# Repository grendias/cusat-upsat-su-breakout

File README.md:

# QB50 SU Connector breakout

A breakout board for the QB50 mNLP Science Unit connector.

## License

Licensed under the [CERN OHLv1.2](LICENSE).

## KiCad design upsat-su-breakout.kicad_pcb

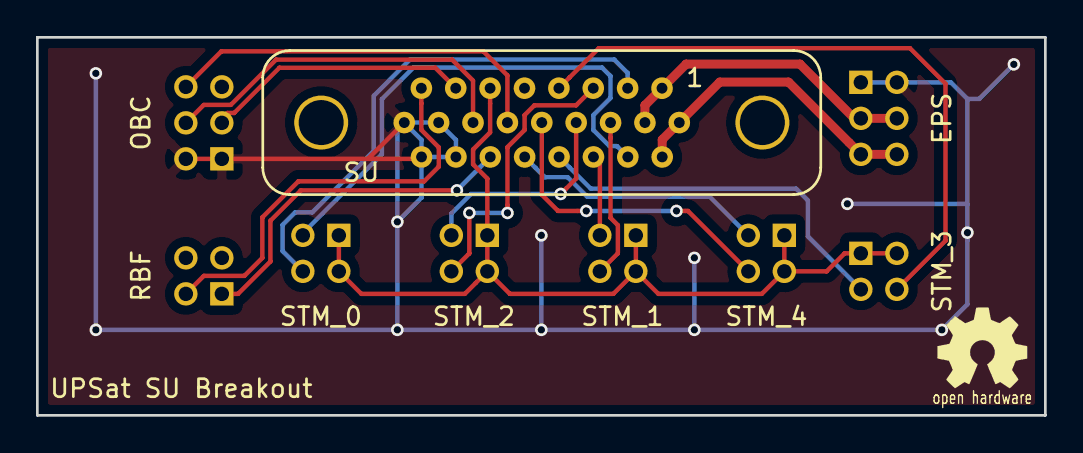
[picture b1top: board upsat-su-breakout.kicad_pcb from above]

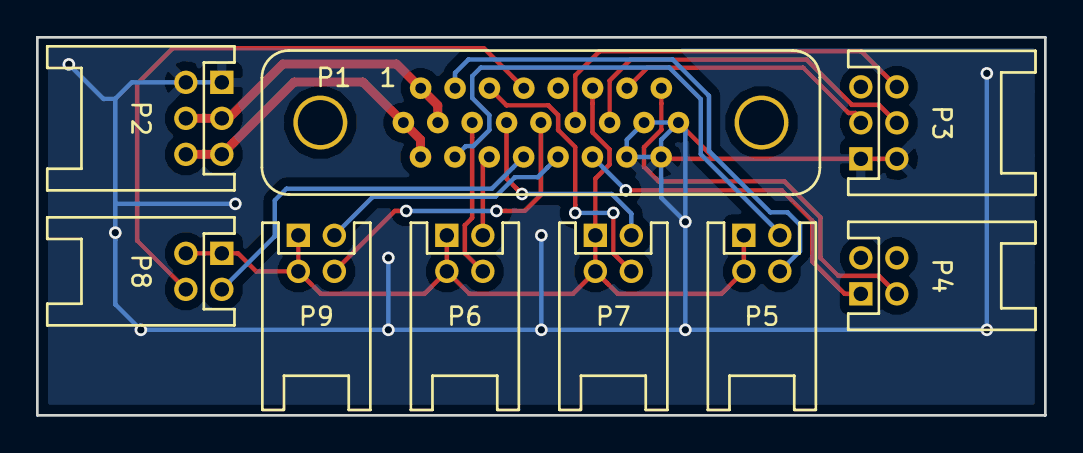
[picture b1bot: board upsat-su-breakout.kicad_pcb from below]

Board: 2 copper layers, 56.0 x 21.0 mm, 9 parts (9 on the bottom side), 19 nets.

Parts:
P1: SU; gmr7580-25p
P2: EPS; hrs-df11-6dp-2ds
P3: OBC; hrs-df11-6dp-2ds
P4: RBF; hrs-df11-4dp-2ds
P5: STM_0; hrs-df11-4dp-2ds
P6: STM_1; hrs-df11-4dp-2ds
P7: STM_2; hrs-df11-4dp-2ds
P8: STM_3; hrs-df11-4dp-2ds
P9: STM_4; hrs-df11-4dp-2ds

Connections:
/+3V3: P1.2, P1.15, P2.3, P2.4
/+5: P1.1, P1.14, P2.5, P2.6
/BIAS_DISARM: P1.12, P4.2
/BIAS_DISARM_GND: P1.22, P4.1
/GND: P1.13, P1.23, P1.24, P1.25, P2.1, P2.2, P3.1, P3.2
/MNLP_RX: P1.10, P3.4
/MNLP_TH_RET: P1.21, P3.6
/MNLP_TX: P1.11, P3.3
/STM_SHIELD: P1.9, P5.1, P5.2, P6.1, P6.2, P7.1, P7.2, P8.1, P8.2, P9.1, P9.2
/STM_TH_GO_0: P1.3, P5.4
/STM_TH_GO_1: P1.4, P6.4
/STM_TH_GO_2: P1.5, P7.4
/STM_TH_GO_3: P1.6, P8.4
/STM_TH_GO_4: P1.7, P9.4
/STM_TH_RET_0: P1.16, P5.3
/STM_TH_RET_1: P1.17, P6.3
/STM_TH_RET_2: P1.18, P7.3
/STM_TH_RET_3: P1.19, P8.3
/STM_TH_RET_4: P1.20, P9.3

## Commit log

2016-03-13 Initial commit.
2016-03-13 Rerouting GND.
2016-03-14 Update layout for better fitting.
2016-03-23 Rerouting some connections.
